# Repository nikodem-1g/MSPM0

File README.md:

# MSPM0 Development board

A compact USB-C powered development board for the Texas Instruments MSPM0G3507 (Arm Cortex-M0+, LQFP-48), designed in KiCad from schematic to PCB layout. Two-layer, 56 × 28 mm. Alongside the microcontroller, the board carries a CH340E USB-UART bridge, an LIS2DH accelerometer on I²C, an 8 MHz crystal, a 3.3 V LDO regulator, and a Tag-Connect TC2030 footprint for SWD programming and debug. Built as a personal project.

Design complete with clean ERC and DRC; not planned for fabrication.

## Rendered PCB

## Schematic

The symbol and footprint for MSPM0 were created from its datasheet because no suitable library entry existed. Power supply, decoupling and clock circuitry follow the manufacturer's datasheet recommendations. The board uses a ground fill with stiching vias, and four M3 mounting holes with fiducials

## Repository contents

```
hardware/   KiCAD project files
docs/       Images and renders
```

## Tools

KiCAD

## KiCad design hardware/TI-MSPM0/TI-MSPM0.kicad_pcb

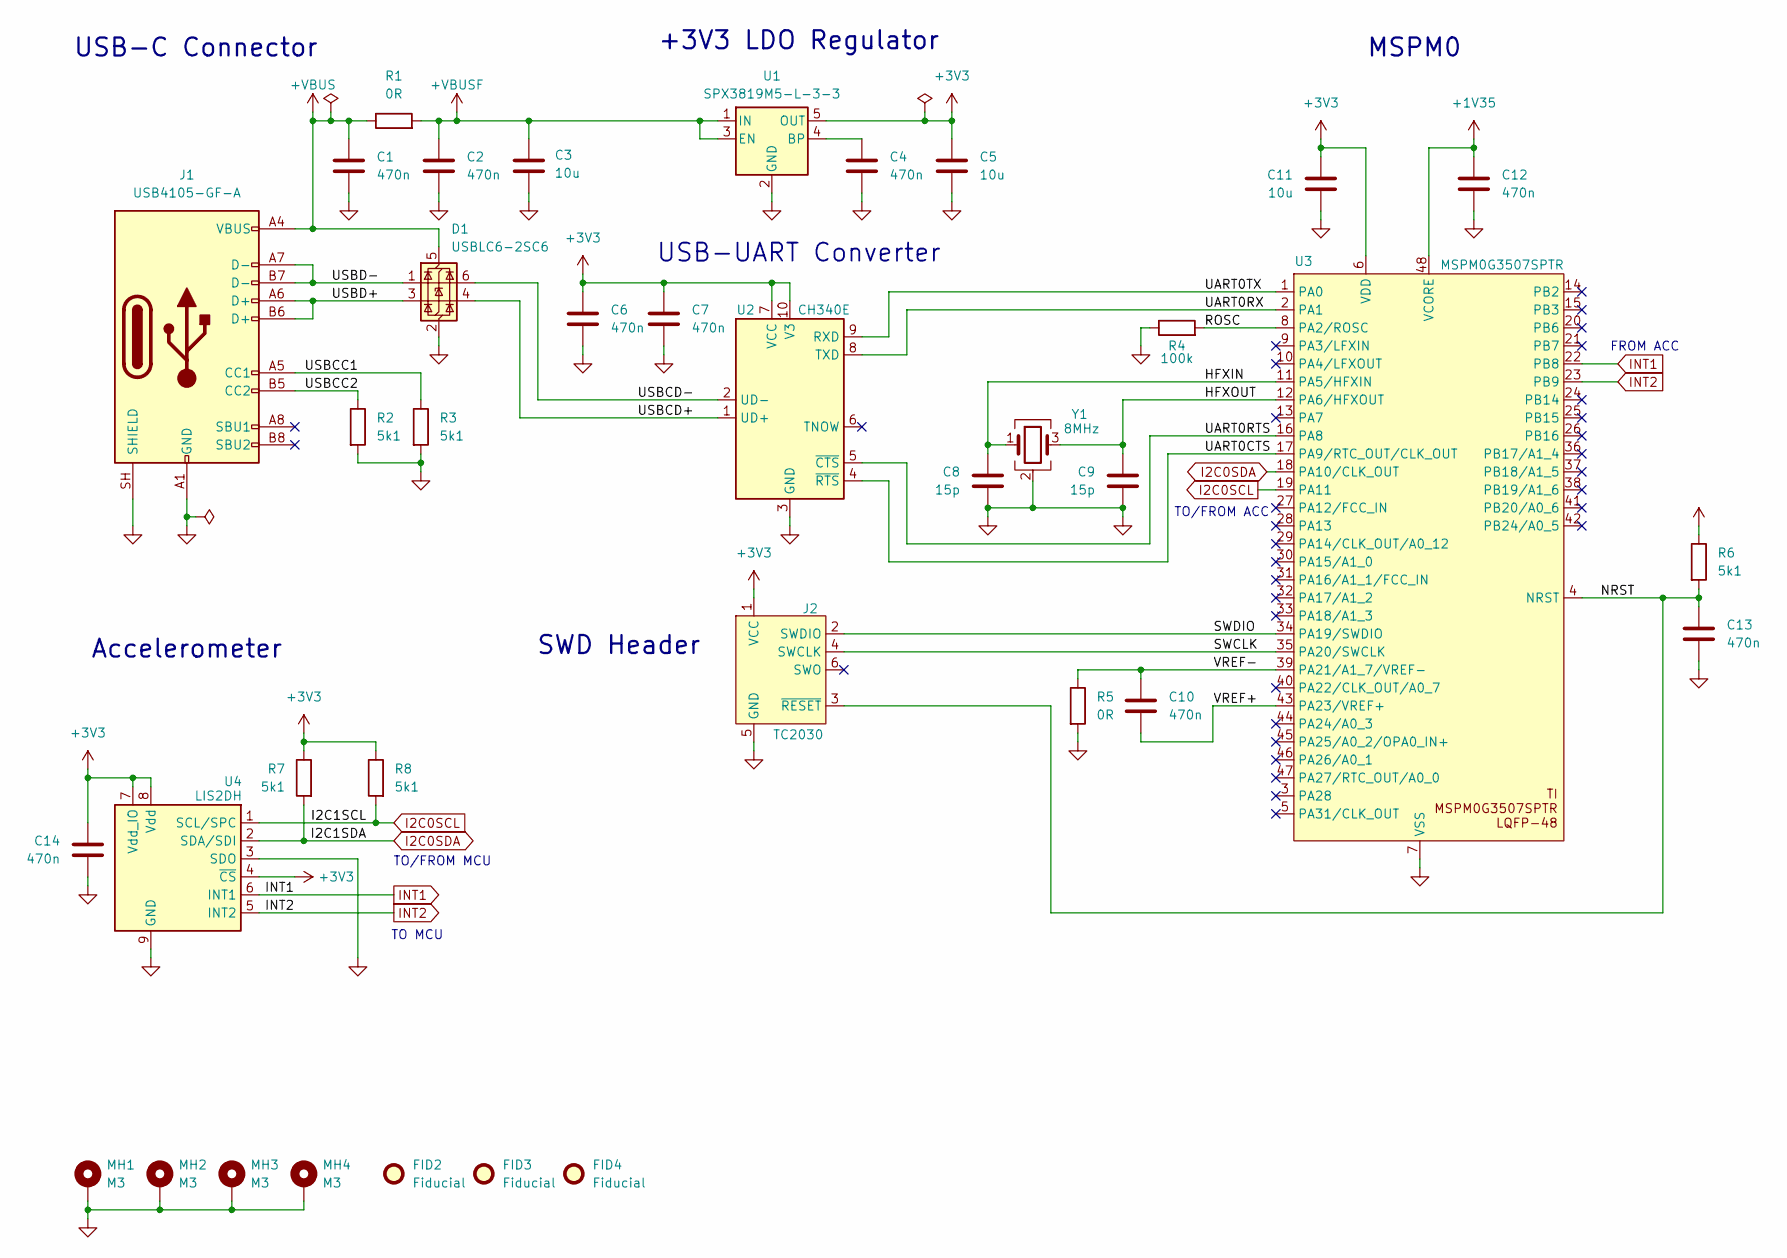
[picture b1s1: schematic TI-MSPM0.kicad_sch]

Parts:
C1, C2, C4, C6, C7, C10, C12, C13, C14: 470n; C_0603_1608Metric
C3, C5, C11: 10u; C_0805_2012Metric
C8, C9: 15p; C_0805_2012Metric
D1: USBLC6-2SC6; SOT-23-6
FID2, FID3, FID4: Fiducial; Fiducial_1mm_Mask2mm
J1: USB4105-GF-A; USB_C_Receptacle_GCT_USB4105-xx-A_16P_TopMnt_Horizontal
J2: TC2030; Tag-Connect_TC2030-IDC-FP_2x03_P1.27mm_Vertical
MH1, MH2, MH3, MH4: M3; MountingHole_3.2mm_M3_Pad_Via
R1, R5: 0R; R_0603_1608Metric
R2, R3, R6, R7, R8: 5k1; R_0603_1608Metric
R4: 100k; R_0603_1608Metric
U1: SPX3819M5-L-3-3; SOT-23-5
U2: CH340E; MSOP-10_3x3mm_P0.5mm
U3: MSPM0G3507SPTR; LQFP-48_7x7mm_P0.5mm; Part Number MSPM0G3507SPTR; LCSC C222362630
U4: LIS2DH; LGA-14_2x2mm_P0.35mm_LayoutBorder3x4y
Y1: 8MHz; Crystal_SMD_3225-4Pin_3.2x2.5mm

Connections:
+1V35: C12.1, U3.48 (VCORE)
+3V3: C5.1, C6.1, C7.1, C11.1, C14.1, J2.1 (VCC), R6.1, R7.1, R8.1, U1.5 (OUT), U2.7 (VCC), U2.10 (V3), U3.6 (VDD), U4.4 (~CS), U4.7 (Vdd_IO), U4.8 (Vdd)
+VBUS: C1.1, D1.5 (VBUS), J1.A4 (VBUS), J1.A9 (VBUS), J1.B4 (VBUS), J1.B9 (VBUS), R1.1
+VBUSF: C2.1, C3.1, R1.2, U1.1 (IN), U1.3 (EN)
/HFXIN: C8.1, U3.11 (PA5/HFXIN), Y1.1
/HFXOUT: C9.1, U3.12 (PA6/HFXOUT), Y1.3
/NRST: C13.1, J2.3 (~RESET), R6.2, U3.4 (NRST)
/ROSC: R4.2, U3.8 (PA2/ROSC)
/SWCLK: J2.4 (SWCLK), U3.35 (PA20/SWCLK)
/SWDIO: J2.2 (SWDIO), U3.34 (PA19/SWDIO)
/UART0CTS: U2.4 (~RTS), U3.17 (PA9/RTC_OUT/CLK_OUT)
/UART0RTS: U2.5 (~CTS), U3.16 (PA8)
/UART0RX: U2.8 (TXD), U3.2 (PA1)
/UART0TX: U2.9 (RXD), U3.1 (PA0)
/USBCC1: J1.A5 (CC1), R3.1
/USBCC2: J1.B5 (CC2), R2.1
/USBCD+: D1.4 (I/O2), U2.1 (UD+)
/USBCD-: D1.6 (I/O1), U2.2 (UD-)
/USBD+: D1.3 (I/O2), J1.A6 (D+), J1.B6 (D+)
/USBD-: D1.1 (I/O1), J1.A7 (D-), J1.B7 (D-)
/VREF+: C10.2, U3.43 (PA23/VREF+)
/VREF-: C10.1, R5.1, U3.39 (PA21/A1_7/VREF-)
GND: C1.2, C2.2, C3.2, C4.2, C5.2, C6.2, C7.2, C8.2, C9.2, C11.2, C12.2, C13.2, C14.2, D1.2 (GND), J1.A1 (GND), J1.A12 (GND), J1.B1 (GND), J1.B12 (GND), J1.SH (SHIELD), J2.5 (GND), MH1.1 (1_1), MH2.1 (1_1), MH3.1 (1_1), MH4.1 (1_1), R2.2, R3.2, R4.1, R5.2, U1.2 (GND), U2.3 (GND), U3.7 (VSS), U4.3 (SDO), U4.9 (GND), Y1.2 (G), Y1.4 (G)
I2C0SCL: R8.2, U3.19 (PA11), U4.1 (SCL/SPC)
I2C0SDA: R7.2, U3.18 (PA10/CLK_OUT), U4.2 (SDA/SDI)
INT1: U3.22 (PB8), U4.6 (INT1)
INT2: U3.23 (PB9), U4.5 (INT2)
unnamed: C4.1, U1.4 (BP)
unnamed: U4.10 (GND), U4.11 (GND), U4.12 (GND), U4.13 (GND), U4.14 (GND)

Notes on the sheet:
TO/FROM MCU
FROM ACC
Accelerometer
+3V3 LDO Regulator
USB-C Connector
MSPM0
TO/FROM ACC
SWD Header
USB-UART Converter
TO MCU

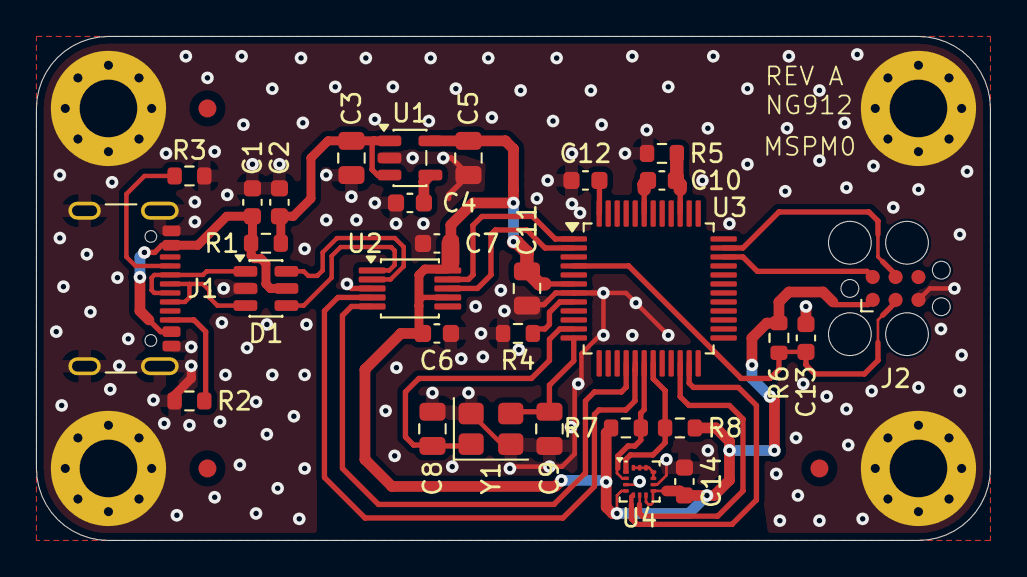
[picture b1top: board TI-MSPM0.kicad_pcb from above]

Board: 2 copper layers, 53.0 x 28.0 mm, 37 parts (0 on the bottom side), 29 nets.
